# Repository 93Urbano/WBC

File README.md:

# WBC
WiFi-Bluetooth CAN-UART Datalogger ESP32
Currenly Desings:
- WBC_02 -> Wifi-Bluetooth-CAN board
  
- WBCR_02 -> Wifi-Bluetooth-CAN and Relays board

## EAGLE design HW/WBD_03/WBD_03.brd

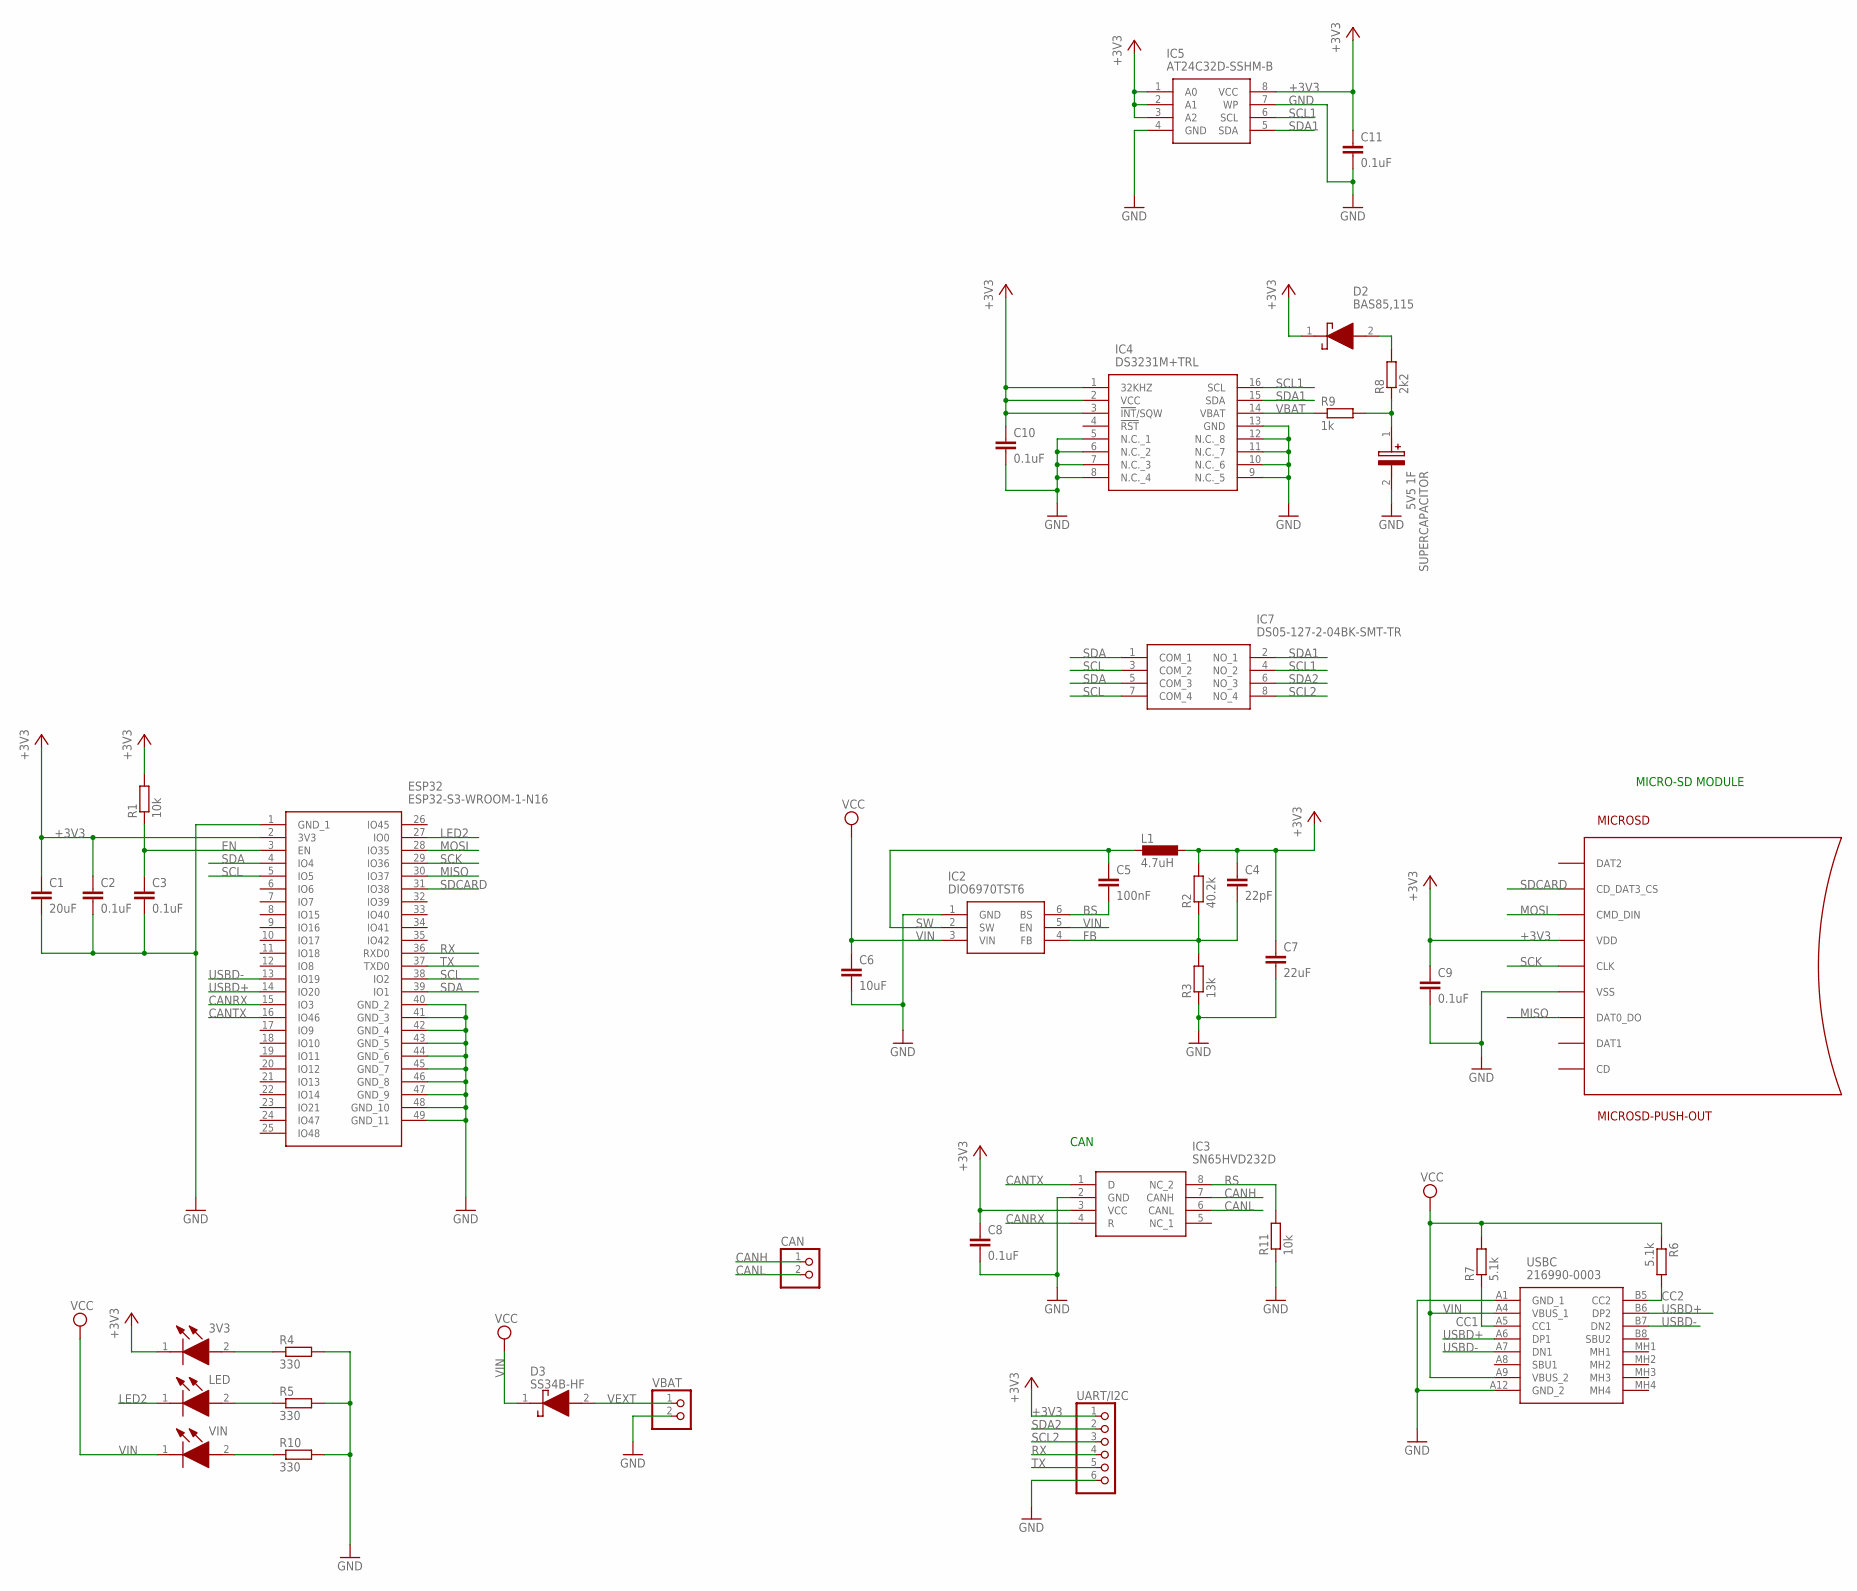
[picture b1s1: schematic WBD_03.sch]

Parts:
3V3: 150060GS75000; LEDC1608X80N
C1: 20uF; C0603
C2, C3, C8, C9, C10, C11: 0.1uF; C0603
C4: 22pF; C0603
C5: 100nF; C0603
C6: 10uF; C0603
C7: 22uF; C0603
CAN: PINHD-1X2; 1X02
D2: BAS85,115; BAS85115
D3: SS34B-HF; DIOM5336X320N
ESP32: ESP32-S3-WROOM-1-N16; ESP32S3WROOM1N16
IC2: DIO6970TST6; SOT95P280X90-6N
IC3: SN65HVD232D; SOIC127P600X175-8N
IC4: DS3231M+TRL; SOIC127P1032X265-16N
IC5: AT24C32D-SSHM-B; SOIC127P600X175-8N
IC7: DS05-127-2-04BK-SMT-TR; DS05127204BKSMTTR
L1: 4.7uH; L5650M
LED: 150060GS75000; LEDC1608X80N
MICROSD: MICROSD-PUSH-OUT
R1, R11: 10k; R0603
R2: 40.2k; R0603
R3: 13k; R0603
R4, R5, R10: 330; R0603
R6, R7: 5.1k; R0603
R8: 2k2; R0603
R9: 1k; R0603
SUPERCAPACITOR: 5V5 1F; CAPPRD500W130D2150H800
UART/I2C: PINHD-1X6; 1X06
USBC: 216990-0003; 2169900003
VBAT: PINHD-1X2; 1X02
VIN: 150060GS75000; LEDC1608X80N

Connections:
+3V3: 3V3.1 (K), C1.1, C2.1, C4.1, C7.1, C8.1, C9.1, C10.1, C11.1, D2.1 (K), ESP32.2 (3V3), IC3.3 (VCC), IC4.1 (32KHZ), IC4.2 (VCC), IC4.3 (!INT!/SQW), IC5.1 (A0), IC5.2 (A1), IC5.3 (A2), IC5.8 (VCC), L1.1, MICROSD.4 (VDD), R1.2, R2.2, UART/I2C.1
BS: C5.2, IC2.6 (BS)
CANH: CAN.1, IC3.7 (CANH)
CANL: CAN.2, IC3.6 (CANL)
CANRX: ESP32.15 (IO3), IC3.4 (R)
CANTX: ESP32.16 (IO46), IC3.1 (D)
CC1: R7.1, USBC.A5 (CC1)
CC2: R6.2, USBC.B5 (CC2)
EN: C3.1, ESP32.3 (EN), R1.1
FB: C4.2, IC2.4 (FB), R2.1, R3.2
GND: C1.2, C2.2, C3.2, C6.2, C7.2, C8.2, C9.2, C10.2, C11.2, ESP32.1 (GND_1), ESP32.40 (GND_2), ESP32.41 (GND_3), ESP32.42 (GND_4), ESP32.43 (GND_5), ESP32.44 (GND_6), ESP32.45 (GND_7), ESP32.46 (GND_8), ESP32.47 (GND_9), ESP32.48 (GND_10), ESP32.49 (GND_11), IC2.1 (GND), IC3.2 (GND), IC4.5 (N.C._1), IC4.6 (N.C._2), IC4.7 (N.C._3), IC4.8 (N.C._4), IC4.9 (N.C._5), IC4.10 (N.C._6), IC4.11 (N.C._7), IC4.12 (N.C._8), IC4.13 (GND), IC5.4 (GND), IC5.7 (WP), MICROSD.6 (VSS), MICROSD.G1 (VSS), MICROSD.G2 (VSS), MICROSD.G3 (VSS), MICROSD.G4 (VSS), R3.1, R4.2, R5.2, R10.2, R11.1, SUPERCAPACITOR.2 (-), UART/I2C.6, USBC.A1 (GND_1), USBC.A12 (GND_2), VBAT.2
LDR1: 3V3.2 (A), R4.1
LDR2: LED.2 (A), R5.1
LDR3: R10.1, VIN.2 (A)
LED2: ESP32.27 (IO0), LED.1 (K)
MISO: ESP32.30 (IO37), MICROSD.7 (DAT0_DO)
MOSI: ESP32.28 (IO35), MICROSD.3 (CMD_DIN)
RS: IC3.8 (NC_2), R11.2
RTCBAT: R8.1, R9.2, SUPERCAPACITOR.1 (+)
RTCD: D2.2 (A), R8.2
RX: ESP32.36 (RXD0), UART/I2C.4
SCK: ESP32.29 (IO36), MICROSD.5 (CLK)
SCL: ESP32.5 (IO5), ESP32.38 (IO2), IC7.3 (COM_2), IC7.7 (COM_4)
SCL1: IC4.16 (SCL), IC5.6 (SCL), IC7.4 (NO_2)
SCL2: IC7.8 (NO_4), UART/I2C.3
SDA: ESP32.4 (IO4), ESP32.39 (IO1), IC7.1 (COM_1), IC7.5 (COM_3)
SDA1: IC4.15 (SDA), IC5.5 (SDA), IC7.2 (NO_1)
SDA2: IC7.6 (NO_3), UART/I2C.2
SDCARD: ESP32.31 (IO38), MICROSD.2 (CD_DAT3_CS)
SW: C5.1, IC2.2 (SW), L1.2
TX: ESP32.37 (TXD0), UART/I2C.5
USBD+: ESP32.14 (IO20), USBC.A6 (DP1), USBC.B6 (DP2)
USBD-: ESP32.13 (IO19), USBC.A7 (DN1), USBC.B7 (DN2)
VBAT: IC4.14 (VBAT), R9.1
VEXT: D3.2 (A), VBAT.1
VIN: C6.1, D3.1 (K), IC2.3 (VIN), IC2.5 (EN), R6.1, R7.2, USBC.A4 (VBUS_1), USBC.A9 (VBUS_2), VIN.1 (K)

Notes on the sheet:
CAN
MICRO-SD MODULE

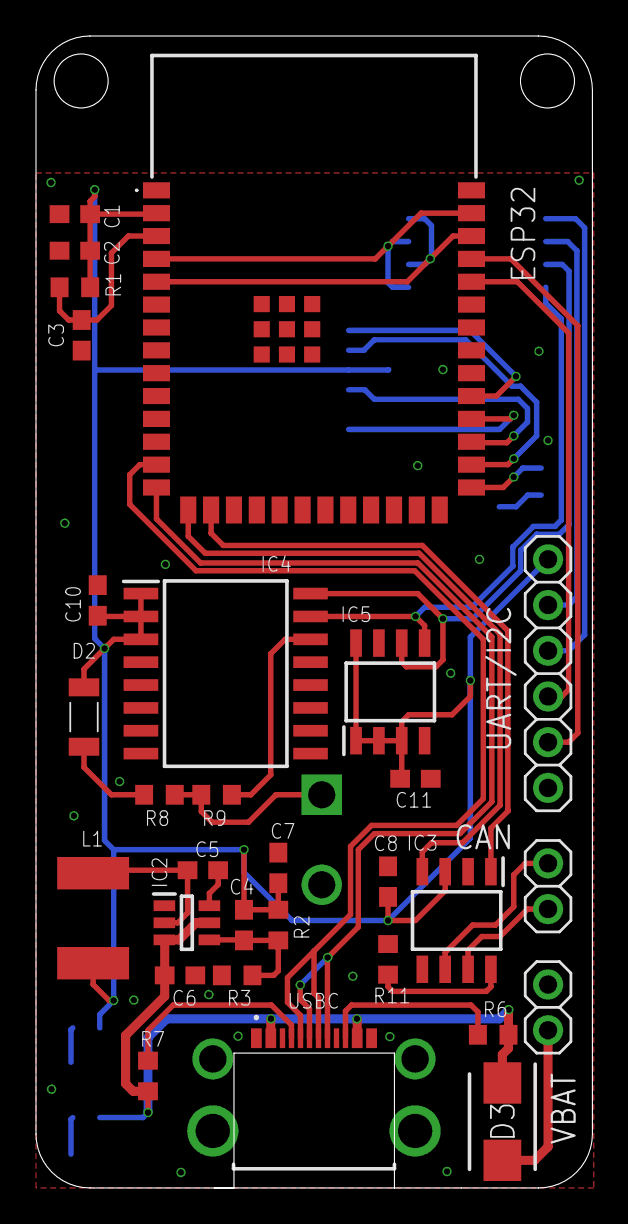
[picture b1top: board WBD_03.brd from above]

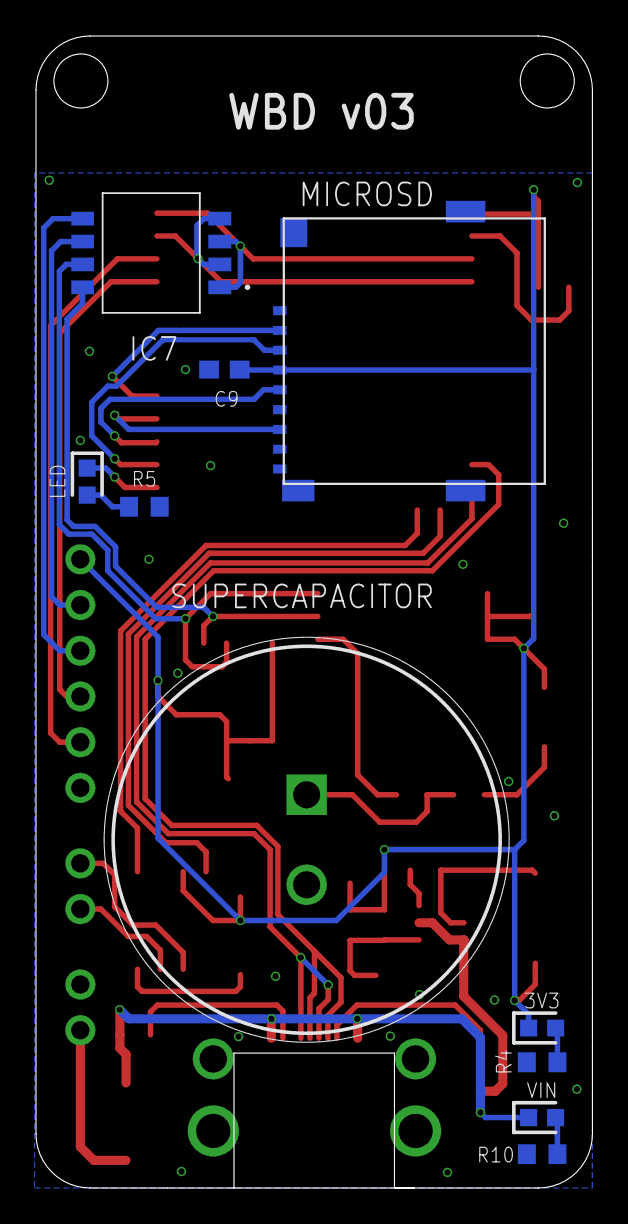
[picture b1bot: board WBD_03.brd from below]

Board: 2 copper layers, 30.9 x 64.0 mm, 40 parts (10 on the bottom side), 36 nets.

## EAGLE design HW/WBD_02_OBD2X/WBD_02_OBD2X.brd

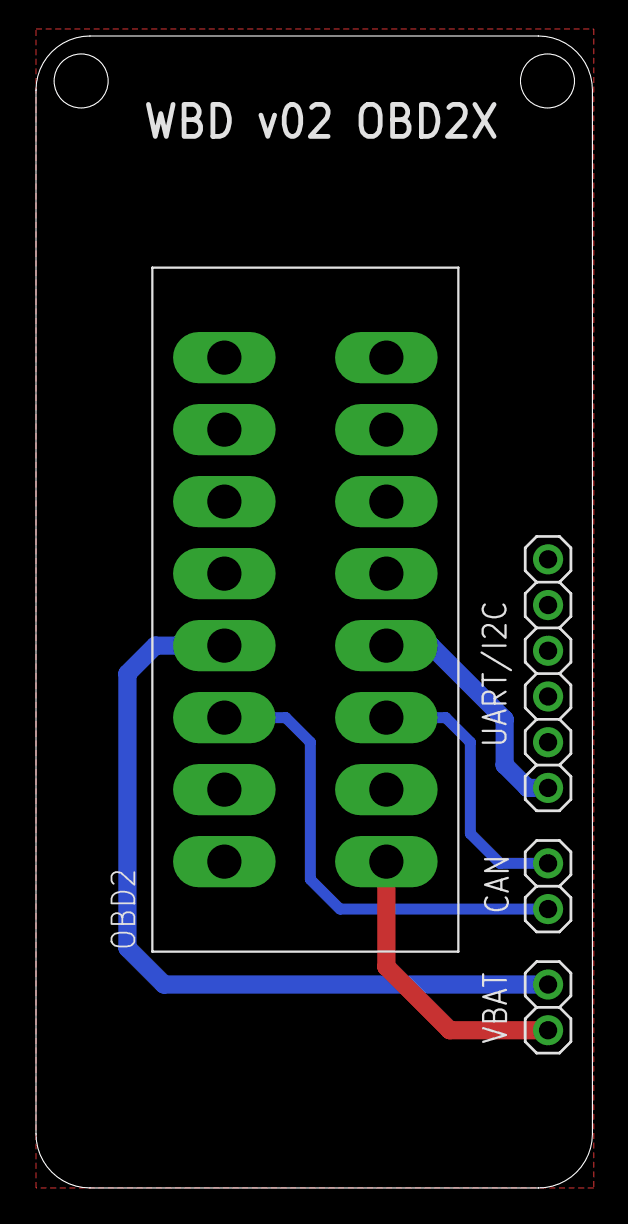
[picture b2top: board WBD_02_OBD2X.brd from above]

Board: 2 copper layers, 30.9 x 64.0 mm, 4 parts (0 on the bottom side), 4 nets.

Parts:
CAN: 1X02
OBD2: OBD2
UART/I2C: 1X06
VBAT: 1X02

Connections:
CANH: CAN.1, OBD2.6
CANL: CAN.2, OBD2.14
GND: OBD2.5, OBD2.13, UART/I2C.6, VBAT.2
VEXT: OBD2.16, VBAT.1

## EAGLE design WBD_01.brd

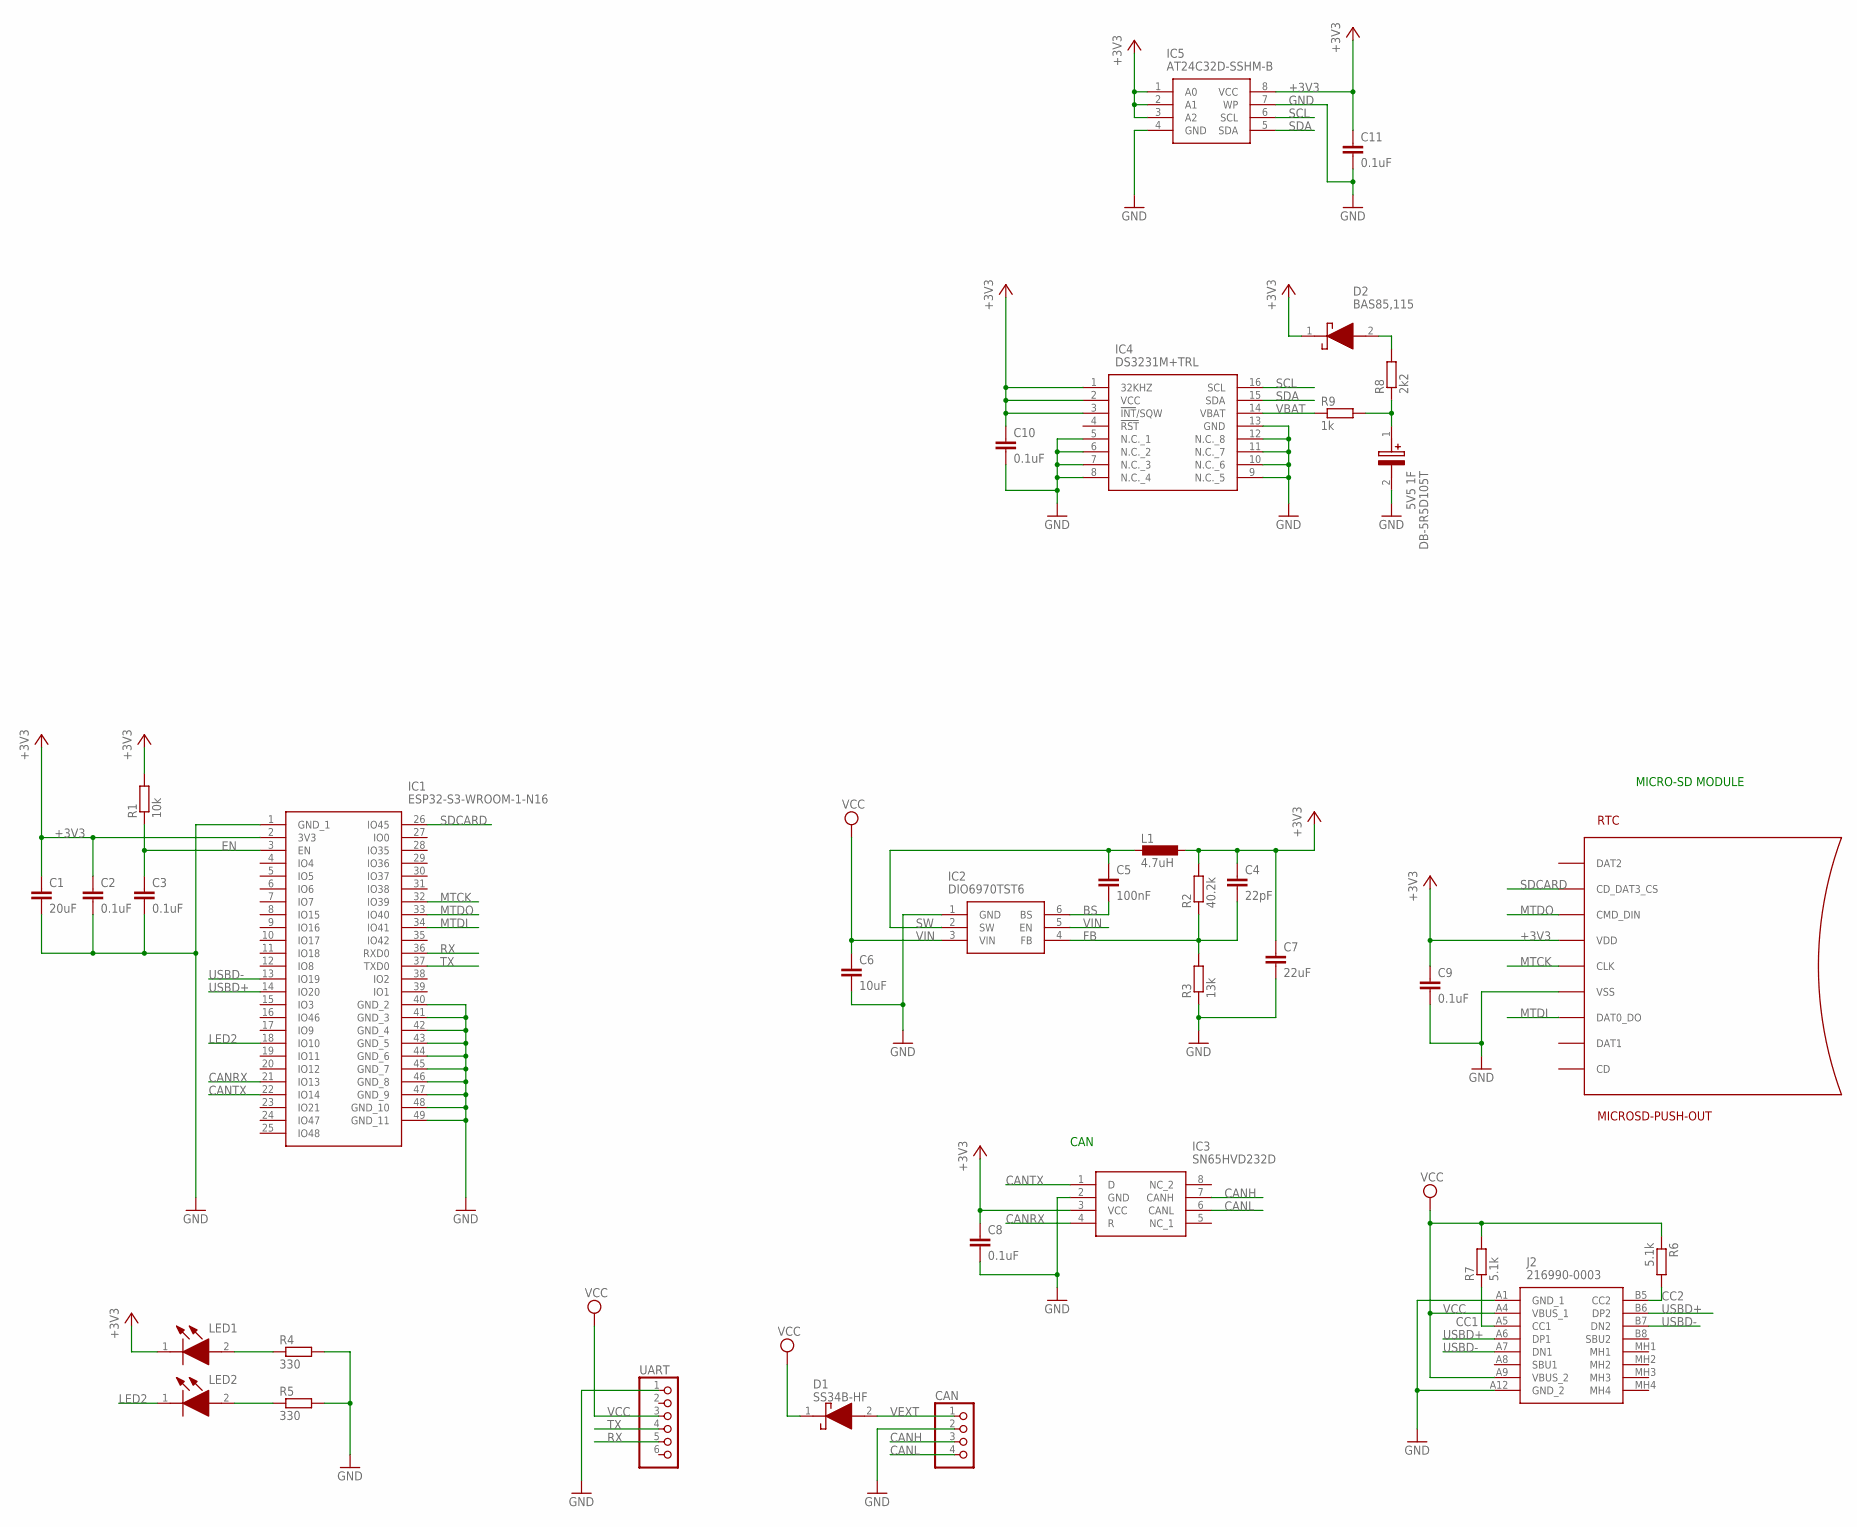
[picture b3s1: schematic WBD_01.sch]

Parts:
C1: 20uF; C0603
C2, C3, C8, C9, C10, C11: 0.1uF; C0603
C4: 22pF; C0603
C5: 100nF; C0603
C6: 10uF; C0603
C7: 22uF; C0603
CAN: PINHD-1X4M; 1X04M
D1: SS34B-HF; DIOM5336X320N
D2: BAS85,115; BAS85115
DB-5R5D105T: 5V5 1F; CAPPRD500W130D2150H800
IC1: ESP32-S3-WROOM-1-N16; ESP32S3WROOM1N16
IC2: DIO6970TST6; SOT95P280X90-6N
IC3: SN65HVD232D; SOIC127P600X175-8N
IC4: DS3231M+TRL; SOIC127P1032X265-16N
IC5: AT24C32D-SSHM-B; SOIC127P600X175-8N
J2: 216990-0003; 2169900003
L1: 4.7uH; L5650M
LED1, LED2: 150060GS75000; LEDC1608X80N
R1: 10k; R0603
R2: 40.2k; R0603
R3: 13k; R0603
R4, R5: 330; R0603
R6, R7: 5.1k; R0603
R8: 2k2; R0603
R9: 1k; R0603
RTC: MICROSD-PUSH-OUT
UART: PINHD-1X6M; 1X06M

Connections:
+3V3: C1.1, C2.1, C4.1, C7.1, C8.1, C9.1, C10.1, C11.1, D2.1 (K), IC1.2 (3V3), IC3.3 (VCC), IC4.1 (32KHZ), IC4.2 (VCC), IC4.3 (!INT!/SQW), IC5.1 (A0), IC5.2 (A1), IC5.3 (A2), IC5.8 (VCC), L1.1, LED1.1 (K), R1.2, R2.2, RTC.4 (VDD)
BS: C5.2, IC2.6 (BS)
CANH: CAN.3, IC3.7 (CANH)
CANL: CAN.4, IC3.6 (CANL)
CANRX: IC1.21 (IO13), IC3.4 (R)
CANTX: IC1.22 (IO14), IC3.1 (D)
CC1: J2.A5 (CC1), R7.1
CC2: J2.B5 (CC2), R6.2
EN: C3.1, IC1.3 (EN), R1.1
FB: C4.2, IC2.4 (FB), R2.1, R3.2
GND: C1.2, C2.2, C3.2, C6.2, C7.2, C8.2, C9.2, C10.2, C11.2, CAN.2, DB-5R5D105T.2 (-), IC1.1 (GND_1), IC1.40 (GND_2), IC1.41 (GND_3), IC1.42 (GND_4), IC1.43 (GND_5), IC1.44 (GND_6), IC1.45 (GND_7), IC1.46 (GND_8), IC1.47 (GND_9), IC1.48 (GND_10), IC1.49 (GND_11), IC2.1 (GND), IC3.2 (GND), IC4.5 (N.C._1), IC4.6 (N.C._2), IC4.7 (N.C._3), IC4.8 (N.C._4), IC4.9 (N.C._5), IC4.10 (N.C._6), IC4.11 (N.C._7), IC4.12 (N.C._8), IC4.13 (GND), IC5.4 (GND), IC5.7 (WP), J2.A1 (GND_1), J2.A12 (GND_2), R3.1, R4.2, R5.2, RTC.6 (VSS), RTC.G1 (VSS), RTC.G2 (VSS), RTC.G3 (VSS), RTC.G4 (VSS), UART.1
LDR1: LED1.2 (A), R4.1
LDR2: LED2.2 (A), R5.1
LED2: IC1.18 (IO10), LED2.1 (K)
MTCK: IC1.32 (IO39), RTC.5 (CLK)
MTDI: IC1.34 (IO41), RTC.7 (DAT0_DO)
MTDO: IC1.33 (IO40), RTC.3 (CMD_DIN)
RTCBAT: DB-5R5D105T.1 (+), R8.1, R9.2
RTCD: D2.2 (A), R8.2
RX: IC1.36 (RXD0), UART.5
SCL: IC4.16 (SCL), IC5.6 (SCL)
SDA: IC4.15 (SDA), IC5.5 (SDA)
SDCARD: IC1.26 (IO45), RTC.2 (CD_DAT3_CS)
SW: C5.1, IC2.2 (SW), L1.2
TX: IC1.37 (TXD0), UART.4
USBD+: IC1.14 (IO20), J2.A6 (DP1), J2.B6 (DP2)
USBD-: IC1.13 (IO19), J2.A7 (DN1), J2.B7 (DN2)
VBAT: IC4.14 (VBAT), R9.1
VCC: D1.1 (K), J2.A4 (VBUS_1), J2.A9 (VBUS_2), R6.1, R7.2, UART.3
VEXT: CAN.1, D1.2 (A)
VIN: C6.1, IC2.3 (VIN), IC2.5 (EN)

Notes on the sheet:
CAN
MICRO-SD MODULE

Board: 2 copper layers, 35 parts (2 on the bottom side), 31 nets, no tracks yet.

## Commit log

2022-11-08 WBD board
2023-02-20 Change CAN and add new board WBDR
2023-04-24 HW finished
2023-09-13 Cambios Overall
2023-09-16 Codigo general y expansion OBD2
2023-10-15 WBC_02_OBD2X Gerbers
2023-10-17 New WBD_03
2023-10-17 Finish WBD_03 + gerbers
2023-12-31 Wifi main server
2023-12-31 Captura de CAN freq fixed
2023-12-31 canOption and canFrequencyControl included as output en CAN config
2023-12-31 UCW web config working
2024-01-01 WiFI included to main
2024-02-16 CAN_BLE
2024-03-31 Add SD and BLE to main
2024-06-10 muchas cosas
